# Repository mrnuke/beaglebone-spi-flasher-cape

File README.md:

# SPI flasher cape for Beaglebone family

## Introduction

The SPI flasher cape is a cape for the BeagleBone family of boards which
allows the BeagleBone to interface with a SPI NOR flash chip in order to allow
programming or reading the chip's contents.

### Features

#### Low BOM cost

The total bill-of-materials (COM) cost is under $10 US, including the PCB.

#### Independent voltage regulator

The independent voltage regulator (VR) supplies the power for the operation of
the SPI chip, and is independent of te BeagleBone's internal voltage rails.
This protects the BeagleBone from brown-outs inc case of an external
short-circuits. Since it is a switching regulator, the VR dissipates very
little power when compared to more common linear regulators.

#### SPI buffer IC

The SPI buffer IC protects the internal pins of the BeagleBone from ESD and
short-circuits. The buffer IC is powered from the independent VR, and prevents
excessive currents from being sourced by the BeagleBone's processor in case of
short-circuits.

The buffer IC is driven by the CS signal of the SPI interface, which means that
the outputs are high-impedance when no SPI communication is taking place. As a
result, the SPI chip does not have to be disconnected when the target system is
powered on. Also, since the buffer is enabled by the CS signal, there is no
extra software configuration that needs to be done before enabling the signal
path to the SPI chip, as there is on other solutions (e.g. Gogole servo board).
It's all automatic!

#### Integrated Cape EEPROM

The integrated EEPROM informs the BeagleBone what pins are used by the cape, so
the cape is automatically detected, and the interfaces pins are automatically
configured.

#### Industry-standard headers for 8-pin and 16-pin SPI devices

The external pin headers match the pinout of 8-pin and 16-pin SPI flash parts
so that programming clips (e.g. Pomona SOIC-8) may be directly connected to the
cape.

#### Integrated pull-up resistors for HOLD and WP lines

The integrated pull-up resistors ensure that the HOLD and WP lines of the SPI
chip are driven appropriately. This allows "naked" chips to be programmed. For
mounted SPI chips, the pull-ups prevent short-circuits if another component on
the target system drives these signals low.

## Layout of the repository

### kicad/

This folder contains the KiCad schematic and board files

* beagleflash-cache.lib:
	project-specific chematic symbol library
* beagleflash.kicad_pcb:
	KiCad (pcbnew) PCB design file
* beagleflash.net:
	Netlist file with footprint associactions
* beagleflash.pro:
	KiCad project file
* beagleflash.sch:
	KiCad (eeschema) schematic

### gerbers/

* beagleflash-B.Cu.gbl:
	Bottom copper layer
* beagleflash-B.Mask.gbs:
	Bottom soldermask layer
* beagleflash-B.SilkS.gbo:
	Bottom silkscreen layer
* beagleflash-Edge.Cuts.gm1:
	Board outline
* beagleflash-F.Cu.gtl:
	Top copper layer
* beagleflash-F.Mask.gts:
	Top soldermask layer
* beagleflash-F.SilkS.gto:
	Top silkscreen layer
* beagleflash.txt:
	Drill file

### pcb_3d_render/

3D renderings of the PCB.

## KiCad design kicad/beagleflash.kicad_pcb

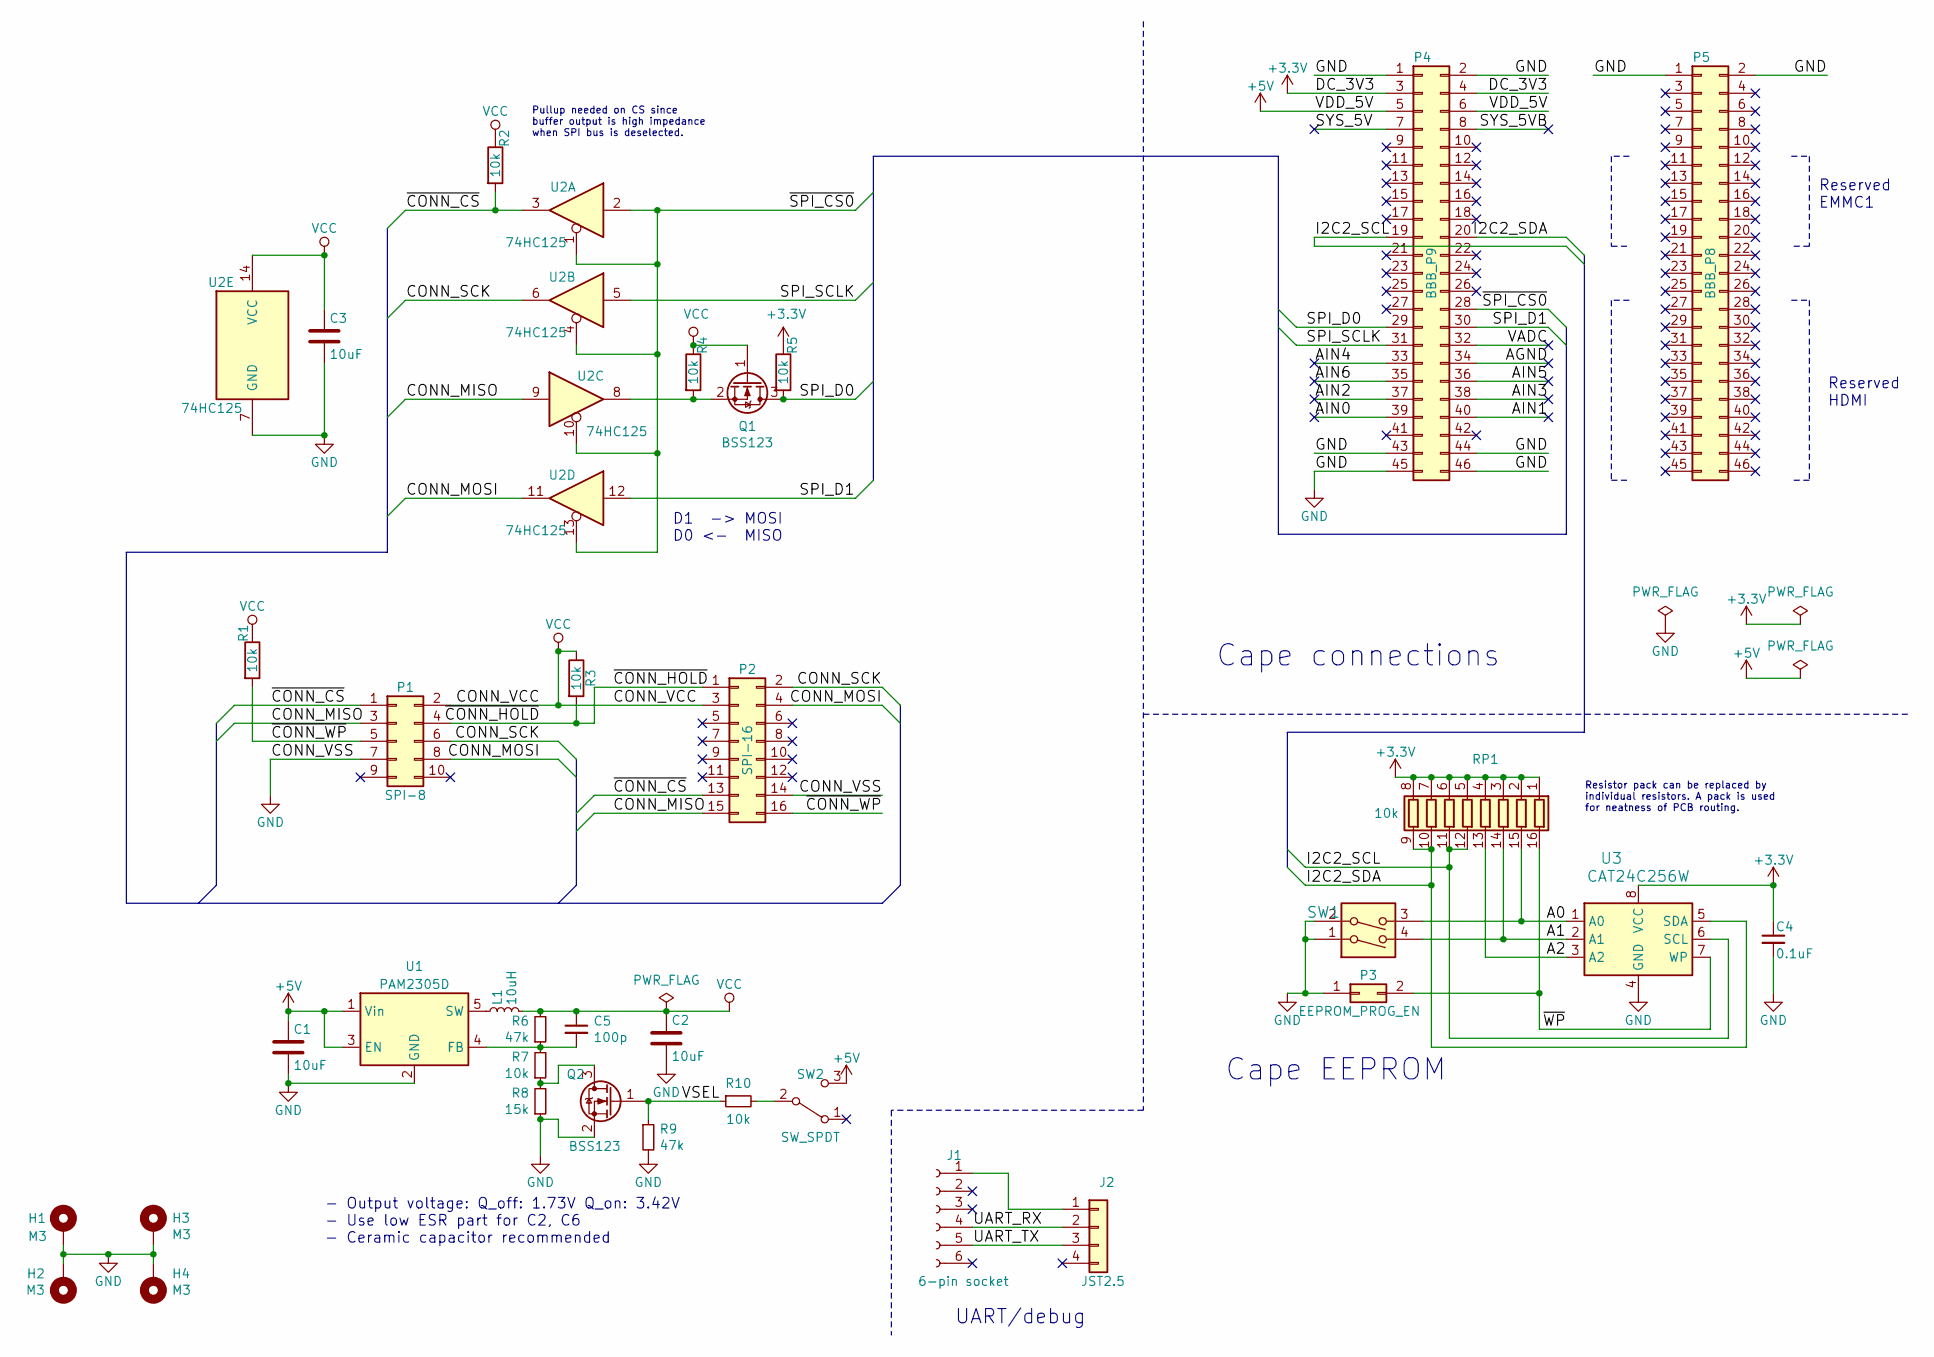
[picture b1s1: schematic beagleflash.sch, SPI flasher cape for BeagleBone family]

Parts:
C1, C2, C3: 10uF; C_0805_2012Metric
C4: 0.1uF; C_0805_2012Metric
C5: 100p; C_0805_2012Metric
H1, H2, H3, H4: M3; MountingHole_3.2mm_M3_ISO14580_Pad
J1: 6-pin socket; PinHeader_1x06_P2.54mm_Vertical
J2: JST2.5; JST_XH_B04B-XH-A_1x04_P2.50mm_Vertical
L1: 10uH; L_1812_4532Metric
P1: SPI-8; IDC-Header_2x05_P2.54mm_Vertical
P2: SPI-16; IDC-Header_2x08_P2.54mm_Vertical
P3: EEPROM_PROG_EN; PinHeader_2x01_P2.54mm_Horizontal
P4: BBB_P9; PinHeader_2x23_P2.54mm_Vertical
P5: BBB_P8; PinHeader_2x23_P2.54mm_Vertical
Q1, Q2: BSS123; SOT-23
R1, R2, R3, R4, R5, R7, R10: 10k; R_0805_2012Metric
R6, R9: 47k; R_0805_2012Metric
R8: 15k; R_0805_2012Metric
RP1: 10k; SOIC-16_3.9x9.9mm_P1.27mm
SW1: DIPS_02; SW_DIP_SPSTx02_Slide_9.78x7.26mm_W7.62mm_P2.54mm
SW2: SW_SPDT; PinHeader_1x03_P2.54mm_Horizontal
U1: PAM2305D; TSOT-23-5
U2: 74HC125; SOIC-14_3.9x8.7mm_P1.27mm
U3: CAT24C256W; SOIC-8_3.9x4.9mm_P1.27mm

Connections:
+3V3: C4.1, P4.3, P4.4, R5.1, RP1.1 (R1.1), RP1.2 (R2.1), RP1.3 (R3.1), RP1.4 (R4.1), RP1.5 (R5.1), RP1.6 (R6.1), RP1.7 (R7.1), RP1.8 (R8.1), U3.8 (VCC)
+5V: C1.1, P4.5, P4.6, SW2.3 (C), U1.1 (Vin), U1.3 (EN)
/A0: RP1.15 (R2.2), SW1.3, U3.1 (A0)
/A1: RP1.14 (R3.2), SW1.4, U3.2 (A1)
/A2: RP1.13 (R4.2), U3.3 (A2)
/AGND: P4.34
/AIN0: P4.39
/AIN1: P4.40
/AIN2: P4.37
/AIN3: P4.38
/AIN4: P4.33
/AIN5: P4.36
/AIN6: P4.35
/CONN_MISO: P1.3, P2.15, U2.9
/CONN_MOSI: P1.8, P2.4, U2.11
/CONN_SCK: P1.6, P2.2, U2.6
/I2C2_SCL: P4.19, RP1.11 (R6.2), RP1.12 (R5.2), U3.6 (SCL)
/I2C2_SDA: P4.20, RP1.9 (R8.2), RP1.10 (R7.2), U3.5 (SDA)
/SPI_D0: P4.29, Q1.3 (D), R5.2
/SPI_D1: P4.30, U2.12
/SPI_SCLK: P4.31, U2.5
/SYS_5V: P4.7
/SYS_5VB: P4.8
/UART_RX: J1.4, J2.2
/UART_TX: J1.5, J2.3
/VADC: P4.32
/VSEL: Q2.1 (G), R9.1, R10.1
/~CONN_CS: P1.1, P2.13, R2.2, U2.3
/~CONN_HOLD: P1.4, P2.1, R3.2
/~CONN_WP: P1.5, P2.16, R1.2
/~SPI_CS0: P4.28, U2.1, U2.2, U2.4, U2.10, U2.13
/~WP: P3.2, RP1.16 (R1.2), U3.7 (WP)
GND: C1.2, C2.2, C3.2, C4.2, H1.1, H2.1, H3.1, H4.1, P1.7, P2.14, P3.1, P4.1, P4.2, P4.43, P4.44, P4.45, P4.46, P5.1, P5.2, Q2.2 (S), R8.1, R9.2, SW1.1, SW1.2, U1.2 (GND), U2.7 (GND), U3.4 (GND)
unnamed: C5.2, R6.1, R7.2, U1.4 (FB)
unnamed: J1.1, J2.1
unnamed: L1.1, U1.5 (SW)
unnamed: Q1.2 (S), R4.2, U2.8
unnamed: Q2.3 (D), R7.1, R8.2
unnamed: R10.2, SW2.2 (B)
VCC: C2.1, C3.1, C5.1, L1.2, P1.2, P2.3, Q1.1 (G), R1.1, R2.1, R3.1, R4.1, R6.2, U2.14 (VCC)

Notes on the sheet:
Reserved EMMC1
Reserved HDMI
Cape EEPROM
Cape connections
- Output voltage: Q_off: 1.73V Q_on: 3.42V - Use low ESR part for C2, C6 - Ceramic capacitor recommended
D1 -> MOSI D0 <- MISO
Pullup needed on CS since buffer output is high impedance when SPI bus is deselected.
Resistor pack can be replaced by individual resistors. A pack is used for neatness of PCB routing.
UART/debug

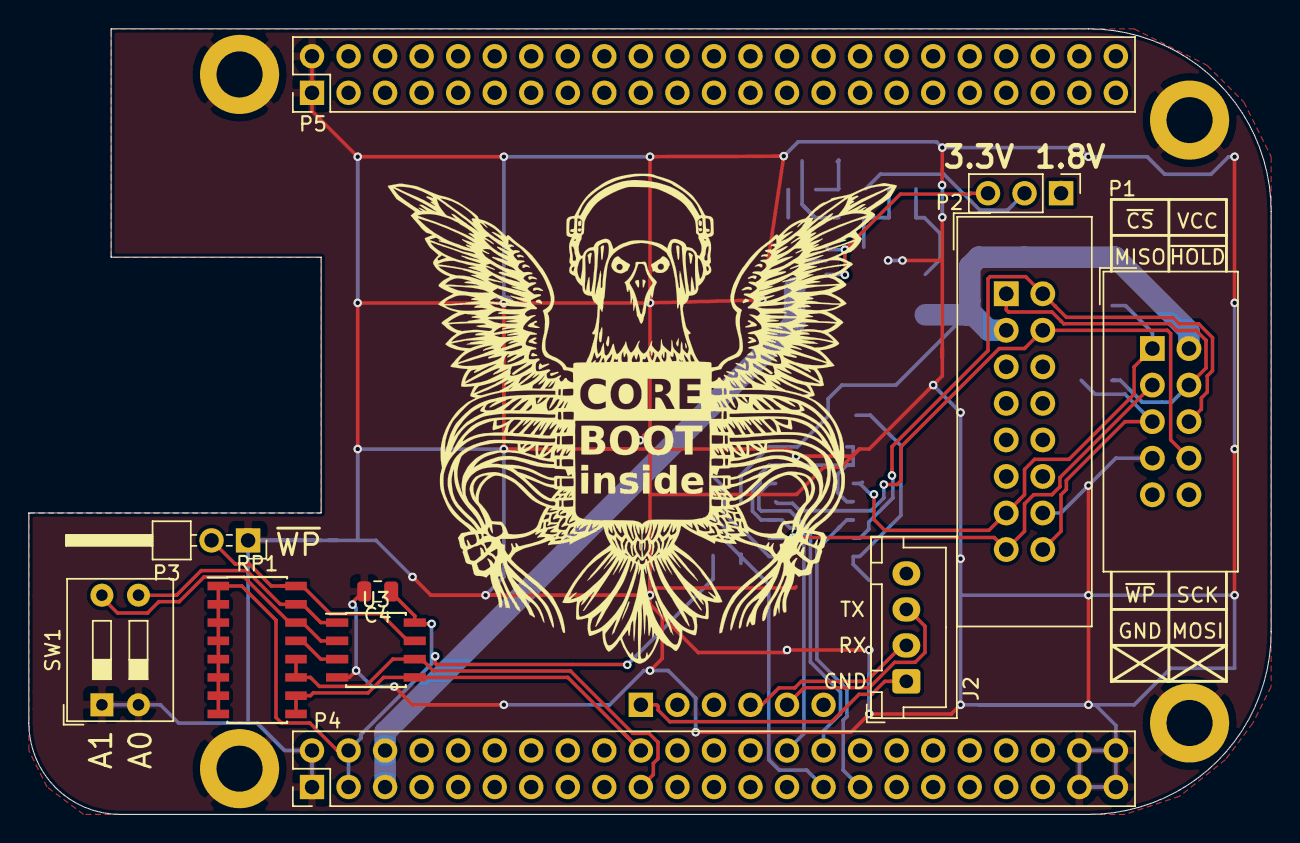
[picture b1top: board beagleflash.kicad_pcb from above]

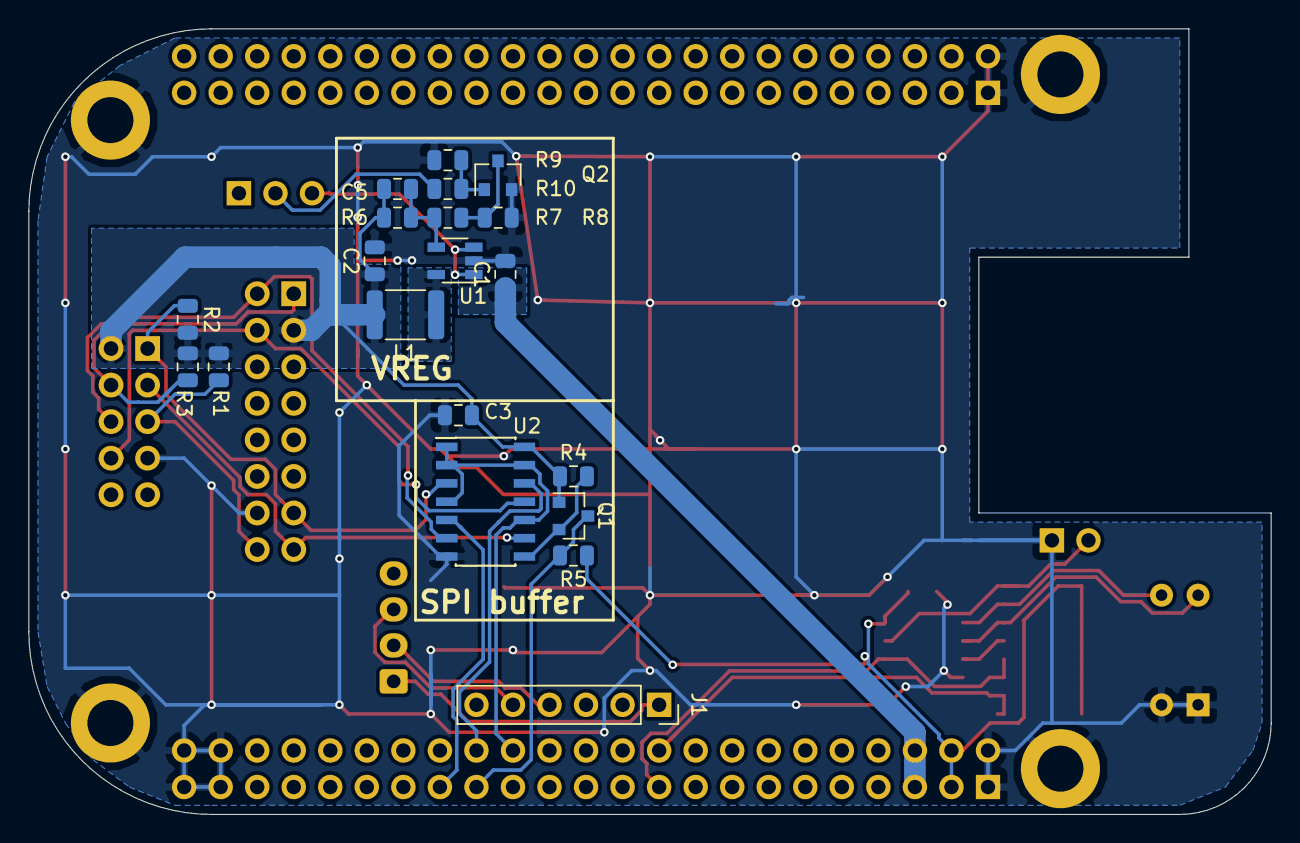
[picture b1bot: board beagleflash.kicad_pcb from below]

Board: 2 copper layers, 86.4 x 54.6 mm, 36 parts (20 on the bottom side), 29 nets.

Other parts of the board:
G1: Logo_Open_Hardware_Small; logo-coreboot

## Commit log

2016-02-04 Add schematic and design files for revision 0.1 of PCB
    This is the beginning, folks! Prototype PCBs are on order.
2016-02-04 Add rendering of Rev 0.1 PCBs
    These prototype PCBs are on order. Only computer-generated renderings
    are available at this time.
2016-02-04 Add gerber files for revision 0.1 PCB
    These are the production files that were sent to the manufacturing
    house for the Rev 0.1 of the PCB.
2016-02-04 Add README.md file with brief description of the design features
2016-10-14 Add .gitignore files
    It's safe to ignore imtermediate files, backup files, backupos to backups
    and so forth, that KiCAD creates.
2016-10-14 kicad: Move logo into stand-alone footprint library
    Otherwise it can easily get lost. This creates a new footprint library
    where all the cape-specific projects will go.
2016-10-14 kicad: Add Revision 0.2 of beagleflash
    Previous revision did not work because the MOSI and MISO pins were
    swapped before the buffer. That's now fixed. Other changes include:
    - Replaced individual resistors around EEPROM with resistor array
    - Added silkscreen designators for SPI pinout on 10-pin header
    - Re-organized DC-DC regulator to have shorter current loops
    - Added exposed GND copper around mounting holes.
2019-03-30 README: Update links to images so that they work with github
    The entire markdown for the image now needs to be on the same line
    for github to pick it up and display the image.
2019-03-30 kicad: Update schematic to use KiCAD 5 symbol library
    A lot has changed in kicad since beagleflash was originally designed.
    KiCAD has a new library format, and it's preferrable to move all the
    symbols to the new format before making any design improvements.
    The is now a symbol for mounting holes with electrical connection:
    * Change mounting hole symbol from connector to MountingHole_Pad.
2019-03-30 kicad: Use the KIPROMOD macro instead of hardcoding library path
2019-04-27 kicad: Add revision 0.3 schematic
    Two incremental changes from rev 0.2:
    * Bring out debug UART to separate header
    * Add 1.8V programming option
    Debug UART:
    Sometimes, it may become necessarry to connect a debug UART to recover
    a bricked beaglebone. Being able to do this without removing the cape
2019-04-28 kicad: Add revision 0.3 layout

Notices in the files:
kicad/beagleflash.sch:
Design and (C) 2016,2019 Alexandru Gagniuc
